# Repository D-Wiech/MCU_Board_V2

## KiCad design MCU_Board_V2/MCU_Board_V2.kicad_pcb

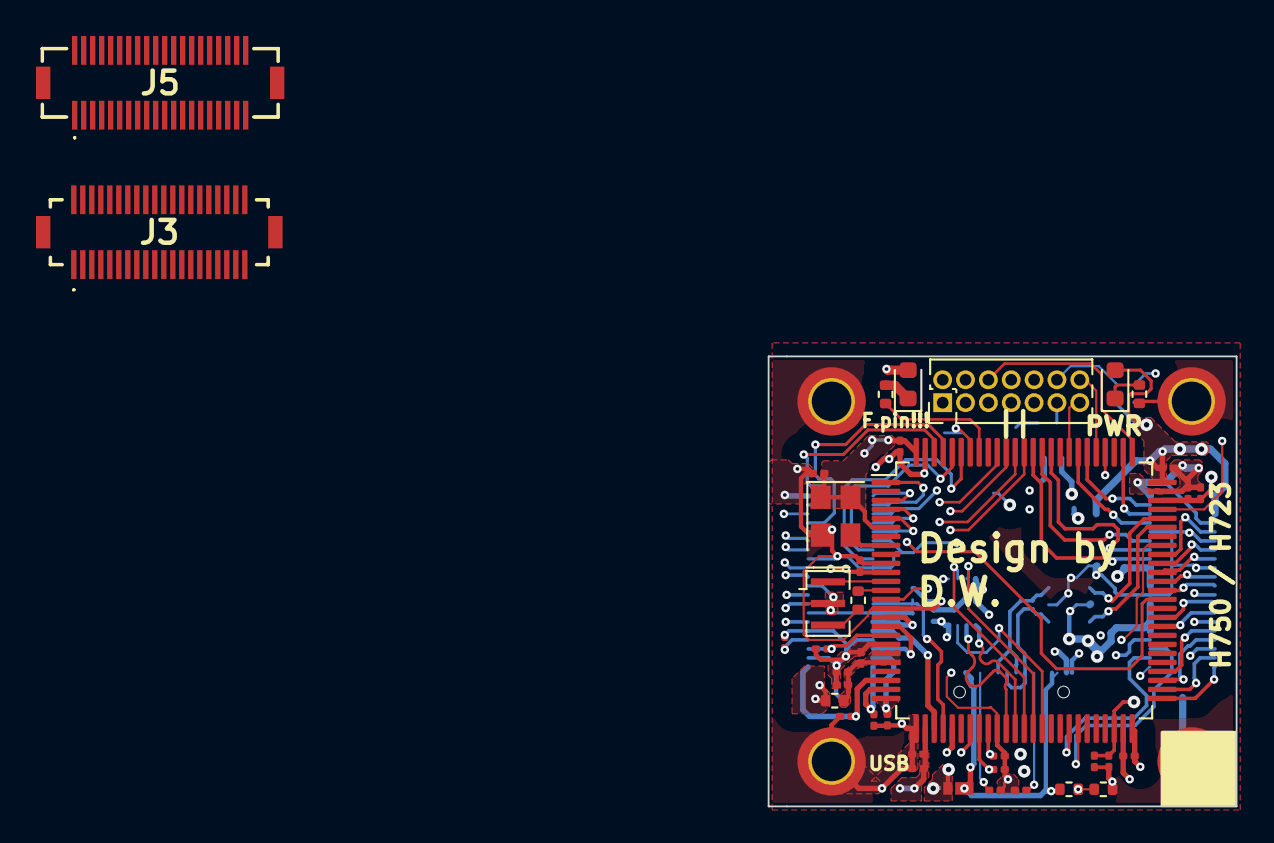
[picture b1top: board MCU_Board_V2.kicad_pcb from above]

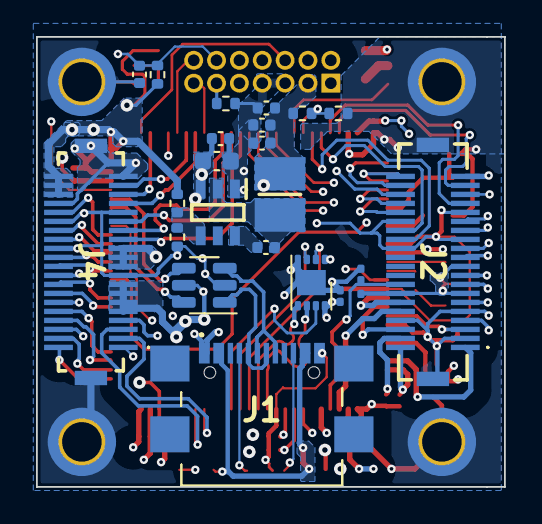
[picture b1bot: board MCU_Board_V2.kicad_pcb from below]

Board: 6 copper layers, 26.0 x 25.0 mm, 65 parts (23 on the bottom side), 80 nets.

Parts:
C_ADC1_IN3, C_ADC1_IN15, C_ADC1_IN17, C_ADC2_IN14, C_ADC3_IN1, C_ADC3_IN11: 10p; C_0201_0603Metric
C_BB1: 100n; C_0201_0603Metric
C_BST_3V1: 100n; C_0402_1005Metric
C_DAC1_OUT1: 10p; C_0201_0603Metric
C_LDO5, C_LDO8, C_LDO10, C_LDO11, C_LDO12, C_LDO16, C_LDO17: 100n; C_0201_0603Metric
C_LDO6, C_LDO7: 4u7; C_0201_0603Metric
C_LDO9, C_LDO13, C_LDO14, C_LDO15, C_LDO18: 1u; C_0201_0603Metric
C_OP_VINM1: 10p; C_0201_0603Metric
C_OP_VINP1: 10p; C_0201_0603Metric
C_Reset1, C_Reset2: 100n; C_0402_1005Metric
C_Vin_3V1: 10u 25V; C_0603_1608Metric
C_Vin_3V2: 100n; C_0402_1005Metric
C_Vout_3V1, C_Vout_3V2: 22u 6V; C_0402_1005Metric
D1: NSR20F30NXT5G; DSN2_1
D_Blue1: PWR; LED_0603_1608Metric
D_Green1: MCU; LED_0603_1608Metric
H1, H2, H3, H4: M2; MountingHole_2.2mm_M2_DIN965_Pad_TopBottom
HSE1: CSTNE8M00GH5C000R0; Resonator_SMD_Murata_CSTxExxV-3Pin_3.0x1.1mm
IC3: AP62200WU-7; SOT95P280X100-6N
J1: USB_C_Receptacle_USB2.0; USB4110GFA
J2, J5: DF12NB_5.0_-40DP-0.5V_51_; DF12NB5040DP05V51
J3, J4: DF12NB-40DS-0.5V_51_; DF12NB40DS05V51
L1: SRP3212A-3R3M; INDC3225X120N
R_BOOT1: DNP; R_0402_1005Metric
R_BOOT2: 30k; R_0402_1005Metric
R_Debug1: 100; R_0402_1005Metric
R_FB_3V1: 31k6; R_0402_1005Metric
R_FB_3V2: 10k; R_0402_1005Metric
R_HSE1: 220; R_0402_1005Metric
R_LED_MCU1: 230; R_0402_1005Metric
R_LED_MCU2: 200; R_0402_1005Metric
R_Reset_1: 30k; R_0402_1005Metric
R_USB1, R_USB2: 5k1; R_0201_0603Metric
R_VBUS1, R_VBUS2: 30k; R_0402_1005Metric
R_filter1: 10; R_0402_1005Metric
STDC1: Conn_01x14_Female; PinHeader_2x07_P1.27mm_Vertical
U4: USBLC6-2SC6; SOT-23-6
U5: STM32H723VGTx; LQFP-100_14x14mm_P0.5mm
U6: ZD25WQ32C; SON-8-1EP_3x2mm_P0.5mm_EP1.4x1.6mm
X1: F322516MUBCE2O; Oscillator_SMD_Abracon_ASE-4Pin_3.2x2.5mm

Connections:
+3.3VA: C_LDO9.1, C_LDO12.1, C_LDO18.1, R_filter1.1, U5.20 (VREF+), U5.21 (VDDA)
+3V3: C_BB1.1, C_LDO8.1, C_LDO10.1, C_LDO11.1, C_LDO13.1, C_LDO14.1, C_LDO15.1, C_LDO17.1, C_Reset2.1, C_Vout_3V1.2, C_Vout_3V2.2, D_Blue1.2 (A), D_Green1.2 (A), J4.19, J4.21, J4.23, J4.36, J4.38, J4.40, L1.2, R_BOOT1.1, R_FB_3V1.1, R_Reset_1.1, R_filter1.2, STDC1.3, U5.6 (VBAT), U5.11 (VDD), U5.27 (VDD), U5.50 (VDD), U5.75 (VDD), U5.100 (VDD), U6.8 (VCC), X1.1 (EN), X1.4 (Vdd)
+5V: C_Vin_3V1.2, C_Vin_3V2.1, D1.1, IC3.3 (VIN), J4.9, J4.11, J4.13, J4.15, U4.5 (VBUS)
/Anschlüsse/CC1: J1.A5 (CC1), R_USB2.1
/Anschlüsse/CC2: J1.B5 (CC2), R_USB1.1
/BST_3V3: C_BST_3V1.2, IC3.6 (BST)
/FB_3V3: IC3.4 (FB), R_FB_3V1.2, R_FB_3V2.1
/MCU/LED_PWR: D_Blue1.1 (K), R_LED_MCU2.1
/MCU/R_GND: R_Debug1.1, STDC1.11
/SW_3V3: C_BST_3V1.1, IC3.2 (SW), L1.1
ADC1_INP3: C_ADC1_IN3.1, J2.7, U5.30 (PA6)
ADC1_INP15: C_ADC1_IN15.1, J2.4, U5.25 (PA3)
ADC1_INP17: C_ADC1_IN17.1, J2.1, U5.23 (PA1)
ADC2_INP14: C_ADC2_IN14.1, J2.2, U5.24 (PA2)
ADC2_INP18: J2.10, U5.28 (PA4)
ADC3_INP0: J2.6, U5.17 (PC2_C)
ADC3_INP11: C_ADC3_IN11.1, J2.12, U5.16 (PC1)
ADC_INP1: C_ADC3_IN1.1, J2.5, U5.18 (PC3_C)
BOOT: R_BOOT1.2, R_BOOT2.1, U5.94 (BOOT0)
DAC1_OUT2: C_DAC1_OUT1.1, J2.16, U5.29 (PA5)
GND: C_ADC1_IN3.2, C_ADC1_IN15.2, C_ADC1_IN17.2, C_ADC2_IN14.2, C_ADC3_IN1.2, C_ADC3_IN11.2, C_BB1.2, C_DAC1_OUT1.2, C_LDO5.2, C_LDO6.2, C_LDO7.2, C_LDO8.2, C_LDO9.2, C_LDO10.2, C_LDO11.2, C_LDO12.2, C_LDO13.2, C_LDO14.2, C_LDO15.2, C_LDO16.2, C_LDO17.2, C_LDO18.2, C_OP_VINM1.2, C_OP_VINP1.2, C_Reset1.2, C_Reset2.2, C_Vin_3V1.1, C_Vin_3V2.2, C_Vout_3V1.1, C_Vout_3V2.1, H1.1, H2.1, H3.1, H4.1, HSE1.2, IC3.1 (GND), J1.A1 (GND), J1.A12 (GND), J1.B1 (GND), J1.B12 (GND), J2.3, J2.8, J2.9, J2.13, J2.14, J2.19, J2.24, J2.25, J2.30, J2.31, J2.36, J2.39, J2.MP1, J2.MP2, J4.1, J4.6, J4.7, J4.12, J4.17, J4.18, J4.24, J4.30, J4.31, J4.34, J4.39, J4.MP1, J4.MP2, R_BOOT2.2, R_Debug1.2, R_FB_3V2.2, R_LED_MCU2.2, R_USB1.2, R_USB2.2, R_VBUS2.1, STDC1.5, STDC1.7, U4.2 (GND), U5.10 (VSS), U5.15 (PC0), U5.19 (VSSA), U5.26 (VSS), U5.35 (PB1), U5.49 (VSS), U5.74 (VSS), U5.99 (VSS), U6.4 (GND), U6.9 (EP), X1.2 (GND)
I2C1_SCL: J2.26, U5.95 (PB8)
I2C1_SDA: J2.28, U5.96 (PB9)
I2C4_SCL: J4.14, U5.59 (PD12)
I2C4_SDA: J4.16, U5.60 (PD13)
LED_MCU: R_LED_MCU1.2, U5.93 (PB7)
unnamed: C_LDO5.1, C_LDO6.1, C_LDO7.1, C_LDO16.1, U5.48 (VCAP), U5.73 (VCAP)
unnamed: D_Green1.1 (K), R_LED_MCU1.1
unnamed: HSE1.3, R_HSE1.2
unnamed: R_VBUS1.1, R_VBUS2.2, U5.68 (PA9)
unnamed: HSE1.1, U5.12 (PH0)
unnamed: R_HSE1.1, U5.13 (PH1)
OPAMP1_VINM: C_OP_VINM1.1, J2.15, U5.33 (PC5)
OPAMP1_VINP: C_OP_VINP1.1, J2.17, U5.34 (PB0)
OPAMP1_VOUT: J2.11, U5.32 (PC4)
OSC37k: U5.8 (PC14), X1.3 (OUT)
QSPI_CLK: U5.36 (PB2), U6.6 (CLK)
QSPI_CS: U5.79 (PC11), U6.1 (~CS)
QSPI_IO0: U5.37 (PE7), U6.5 (DI(IO0))
QSPI_IO1: U5.38 (PE8), U6.2 (DO(IO1))
QSPI_IO2: U5.39 (PE9), U6.3 (IO2)
QSPI_IO3: U5.40 (PE10), U6.7 (IO3)
RCC_MCO: J4.32, U5.67 (PA8)
SPI4_CS: J2.40, U5.3 (PE4)
SPI4_MISO: J2.34, U5.4 (PE5)
SPI4_MOSI: J2.32, U5.5 (PE6)
SPI4_SCK: J2.38, U5.1 (PE2)
SPI6_CS: J2.21, U5.88 (PD7)
SPI6_MISO: J2.27, U5.90 (PB4(NJTRST))
SPI6_MOSI: J2.29, U5.91 (PB5)
SPI6_SCK: J2.23, U5.89 (PB3(JTDO)
SPI_2_CS: J4.2, U5.51 (PB12)
SPI_2_MISO: J4.8, U5.53 (PB14)
SPI_2_MOSI: J4.10, U5.54 (PB15)
SPI_2_SCLK: J4.4, U5.52 (PB13)
SWCLK: STDC1.6, U5.76 (PA14(JTCK)
SWDIO: STDC1.4, U5.72 (PA13(JTMS)
TIM1_CH3: J4.3, U5.43 (PE13)
TIM1_CH4: J4.5, U5.44 (PE14)
TIM8_CH1: J4.20, U5.63 (PC6)
TIM8_CH2: J4.22, U5.64 (PC7)
TIM8_CH3: J4.26, U5.65 (PC8)
TIM8_CH4: J4.28, U5.66 (PC9)
UART4_DE: J4.35, U5.77 (PA15(JTDI))
UART4_RX: J4.37, U5.81 (PD0)
UART4_TX: J4.33, U5.82 (PD1)
UART5_RX: STDC1.13, U5.83 (PD2)
UART5_TX: STDC1.14, U5.80 (PC12)
UART8_DE: J2.35, U5.62 (PD15)
UART8_RX: J2.33, U5.97 (PE0)
UART8_TX: J2.37, U5.98 (PE1)
USART2_DE: J4.27, U5.85 (PD4)
USART2_RX: J4.25, U5.87 (PD6)
USART2_TX: J4.29, U5.86 (PD5)
USB_CONN_D+: J1.A6 (D+), J1.B6 (D+), U4.3 (I/O2)
USB_CONN_D-: J1.A7 (D-), J1.B7 (D-), U4.1 (I/O1)
USB_D+: U4.4 (I/O2), U5.71 (PA12)
USB_D-: U4.6 (I/O1), U5.70 (PA11)
VBUS: D1.2, J1.A4 (VBUS), J1.A9 (VBUS), J1.B4 (VBUS), J1.B9 (VBUS), R_VBUS1.2
nRST: C_Reset1.1, R_Reset_1.2, STDC1.12, U5.14 (NRST)

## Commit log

2024-01-24 Finished design for aisler.
    NPTH of the USB have an issue
2024-01-25 Adjusted for JLC as manufacturer
